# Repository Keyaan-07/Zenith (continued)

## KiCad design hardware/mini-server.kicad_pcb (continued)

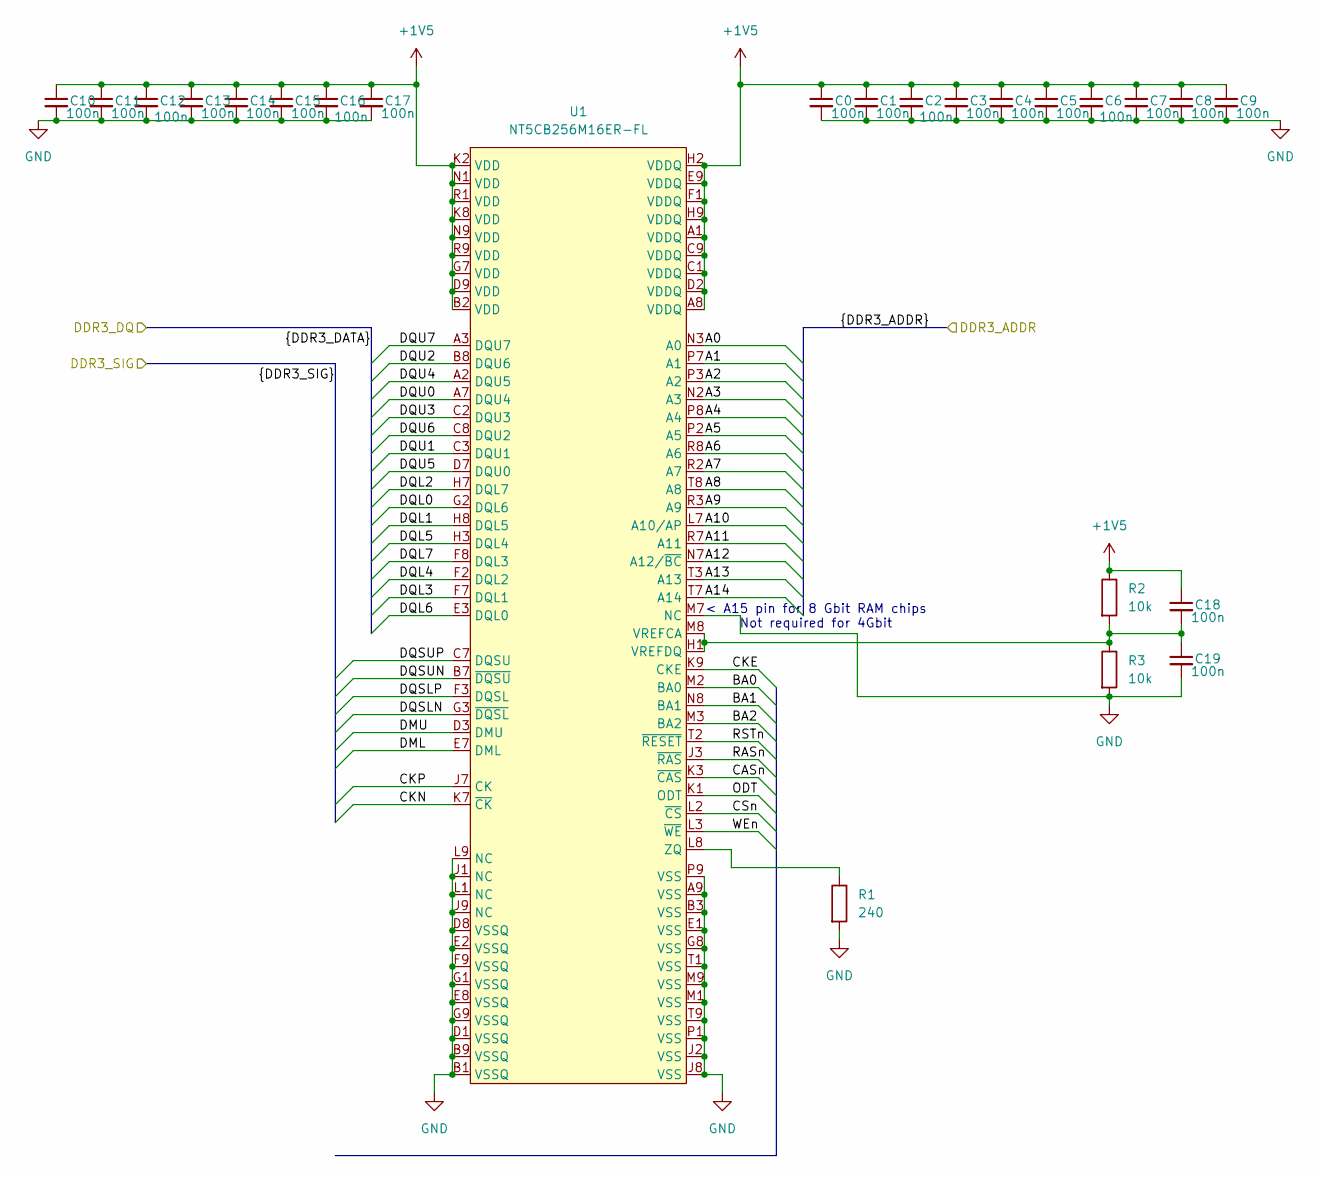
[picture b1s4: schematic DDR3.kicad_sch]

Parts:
C0, C1, C2, C3, C4, C5, C6, C7, C8, C9, C10, C11, C12, C13, C14, C15, C16, C17, C18, C19: 100n; C_0201_0603Metric
R1: 240; R_0201_0603Metric
R2, R3: 10k; R_0201_0603Metric
U1: NT5CB256M16ER-FL; TFBGA-96_L13.0-W8.0-R16-C6-P0.80-TL; MPN NT5CB256M16ER-FL; LCSC Part C2841154

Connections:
+1V5: C0.1, C1.1, C2.1, C3.1, C4.1, C5.1, C6.1, C7.1, C8.1, C9.1, C10.1, C11.1, C12.1, C13.1, C14.1, C15.1, C16.1, C17.1, C18.1, R2.1, U1.A1 (VDDQ), U1.A8 (VDDQ), U1.B2 (VDD), U1.C1 (VDDQ), U1.C9 (VDDQ), U1.D2 (VDDQ), U1.D9 (VDD), U1.E9 (VDDQ), U1.F1 (VDDQ), U1.G7 (VDD), U1.H2 (VDDQ), U1.H9 (VDDQ), U1.K2 (VDD), U1.K8 (VDD), U1.N1 (VDD), U1.N9 (VDD), U1.R1 (VDD), U1.R9 (VDD); also elsewhere on the board
/DDR3/A0: U1.N3 (A0); also elsewhere on the board
/DDR3/A1: U1.P7 (A1); also elsewhere on the board
/DDR3/A2: U1.P3 (A2); also elsewhere on the board
/DDR3/A3: U1.N2 (A3); also elsewhere on the board
/DDR3/A4: U1.P8 (A4); also elsewhere on the board
/DDR3/A5: U1.P2 (A5); also elsewhere on the board
/DDR3/A6: U1.R8 (A6); also elsewhere on the board
/DDR3/A7: U1.R2 (A7); also elsewhere on the board
/DDR3/A8: U1.T8 (A8); also elsewhere on the board
/DDR3/A9: U1.R3 (A9); also elsewhere on the board
/DDR3/A10: U1.L7 (A10/AP); also elsewhere on the board
/DDR3/A11: U1.R7 (A11); also elsewhere on the board
/DDR3/A12: U1.N7 (A12/~BC); also elsewhere on the board
/DDR3/A13: U1.T3 (A13); also elsewhere on the board
/DDR3/A14: U1.T7 (A14); also elsewhere on the board
/DDR3/BA0: U1.M2 (BA0); also elsewhere on the board
/DDR3/BA1: U1.N8 (BA1); also elsewhere on the board
/DDR3/BA2: U1.M3 (BA2); also elsewhere on the board
/DDR3/CASn: U1.K3 (~CAS); also elsewhere on the board
/DDR3/CKE: U1.K9 (CKE); also elsewhere on the board
/DDR3/CKN: U1.K7 (~CK); also elsewhere on the board
/DDR3/CKP: U1.J7 (CK); also elsewhere on the board
/DDR3/CSn: U1.L2 (~CS); also elsewhere on the board
/DDR3/DML: U1.E7 (DML); also elsewhere on the board
/DDR3/DMU: U1.D3 (DMU); also elsewhere on the board
/DDR3/DQL0: U1.G2 (DQL6); also elsewhere on the board
/DDR3/DQL1: U1.H8 (DQL5); also elsewhere on the board
/DDR3/DQL2: U1.H7 (DQL7); also elsewhere on the board
/DDR3/DQL3: U1.F7 (DQL1); also elsewhere on the board
/DDR3/DQL4: U1.F2 (DQL2); also elsewhere on the board
/DDR3/DQL5: U1.H3 (DQL4); also elsewhere on the board
/DDR3/DQL6: U1.E3 (DQL0); also elsewhere on the board
/DDR3/DQL7: U1.F8 (DQL3); also elsewhere on the board
/DDR3/DQSLN: U1.G3 (~DQSL); also elsewhere on the board
/DDR3/DQSLP: U1.F3 (DQSL); also elsewhere on the board
/DDR3/DQSUN: U1.B7 (~DQSU); also elsewhere on the board
/DDR3/DQSUP: U1.C7 (DQSU); also elsewhere on the board
/DDR3/DQU0: U1.A7 (DQU4); also elsewhere on the board
/DDR3/DQU1: U1.C3 (DQU1); also elsewhere on the board
/DDR3/DQU2: U1.B8 (DQU6); also elsewhere on the board
/DDR3/DQU3: U1.C2 (DQU3); also elsewhere on the board
/DDR3/DQU4: U1.A2 (DQU5); also elsewhere on the board
/DDR3/DQU5: U1.D7 (DQU0); also elsewhere on the board
/DDR3/DQU6: U1.C8 (DQU2); also elsewhere on the board
/DDR3/DQU7: U1.A3 (DQU7); also elsewhere on the board
/DDR3/ODT: U1.K1 (ODT); also elsewhere on the board
/DDR3/RASn: U1.J3 (~RAS); also elsewhere on the board
/DDR3/RSTn: U1.T2 (~RESET); also elsewhere on the board
/DDR3/WEn: U1.L3 (~WE); also elsewhere on the board
GND: C0.2, C1.2, C2.2, C3.2, C4.2, C5.2, C6.2, C7.2, C8.2, C9.2, C10.2, C11.2, C12.2, C13.2, C14.2, C15.2, C16.2, C17.2, C19.2, R1.2, R3.2, U1.A9 (VSS), U1.B1 (VSSQ), U1.B3 (VSS), U1.B9 (VSSQ), U1.D1 (VSSQ), U1.D8 (VSSQ), U1.E1 (VSS), U1.E2 (VSSQ), U1.E8 (VSSQ), U1.F9 (VSSQ), U1.G1 (VSSQ), U1.G8 (VSS), U1.G9 (VSSQ), U1.J1 (NC), U1.J2 (VSS), U1.J8 (VSS), U1.J9 (NC), U1.L1 (NC), U1.L9 (NC), U1.M1 (VSS), U1.M7 (NC), U1.M9 (VSS), U1.P1 (VSS), U1.P9 (VSS), U1.T1 (VSS), U1.T9 (VSS); also elsewhere on the board
unnamed: C18.2, C19.1, R2.2, R3.1, U1.H1 (VREFDQ), U1.M8 (VREFCA)
unnamed: R1.1, U1.L8 (ZQ)

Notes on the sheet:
< A15 pin for 8 Gbit RAM chips Not required for 4Gbit

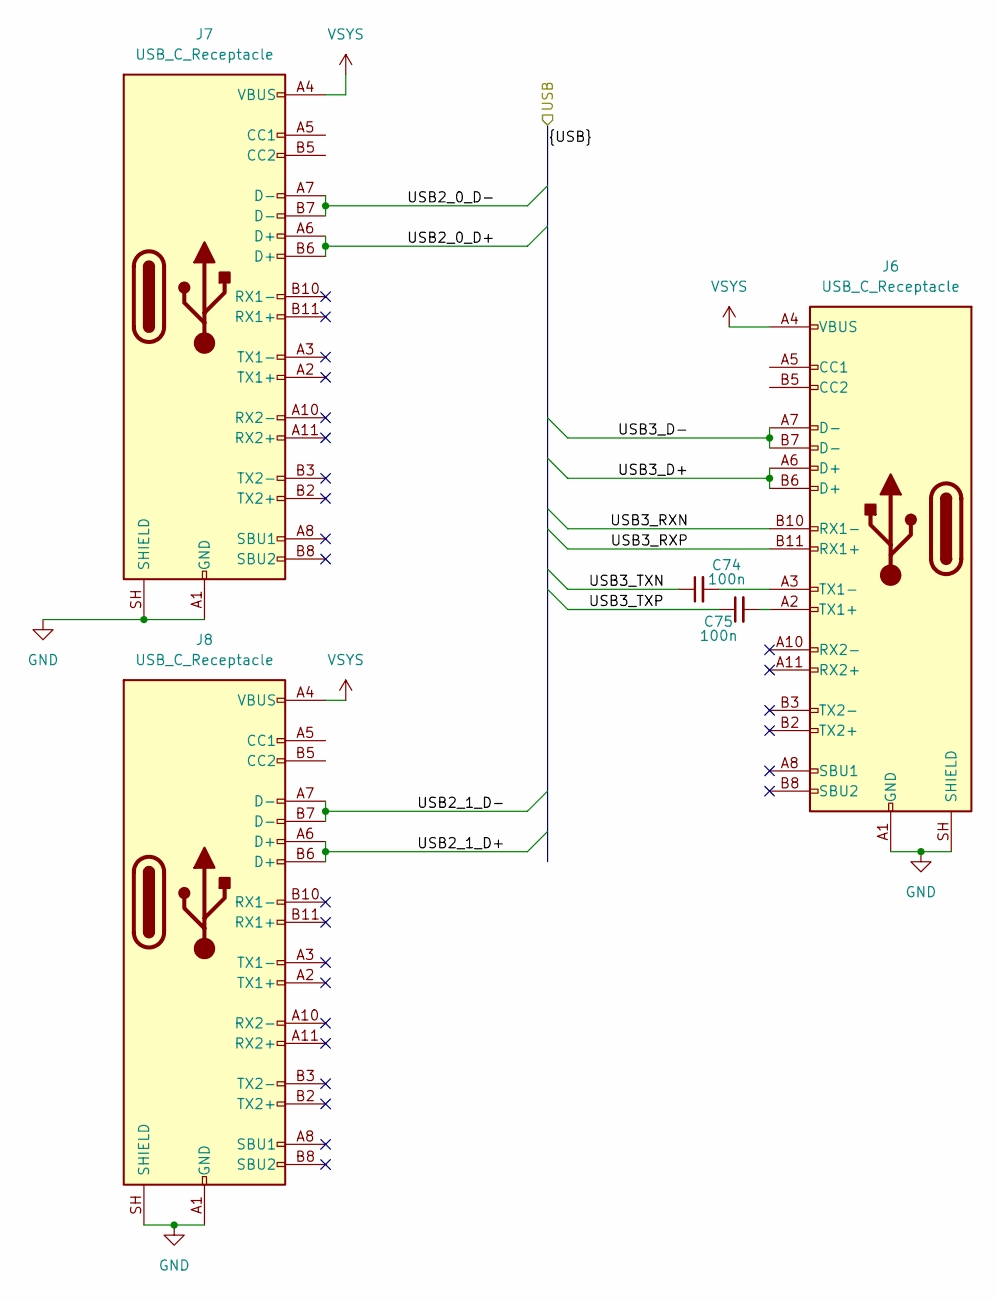
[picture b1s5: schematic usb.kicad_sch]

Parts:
C74, C75: 100n; C_0201_0603Metric
J6, J7, J8: USB_C_Receptacle; USB_C_Receptacle_Molex_105450-0101

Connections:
/USB/USB2_0_D+: J7.A6 (D+), J7.B6 (D+); also elsewhere on the board
/USB/USB2_0_D-: J7.A7 (D-), J7.B7 (D-); also elsewhere on the board
/USB/USB2_1_D+: J8.A6 (D+), J8.B6 (D+); also elsewhere on the board
/USB/USB2_1_D-: J8.A7 (D-), J8.B7 (D-); also elsewhere on the board
/USB/USB3_D+: J6.A6 (D+), J6.B6 (D+); also elsewhere on the board
/USB/USB3_D-: J6.A7 (D-), J6.B7 (D-); also elsewhere on the board
/USB/USB3_RXN: J6.B10 (RX1-); also elsewhere on the board
/USB/USB3_RXP: J6.B11 (RX1+); also elsewhere on the board
/USB/USB3_TXN: C74.1; also elsewhere on the board
/USB/USB3_TXP: C75.1; also elsewhere on the board
GND: J6.A1 (GND), J6.A12 (GND), J6.B1 (GND), J6.B12 (GND), J6.SH (SHIELD), J7.A1 (GND), J7.A12 (GND), J7.B1 (GND), J7.B12 (GND), J7.SH (SHIELD), J8.A1 (GND), J8.A12 (GND), J8.B1 (GND), J8.B12 (GND), J8.SH (SHIELD); also elsewhere on the board
unnamed: C75.2, J6.A2 (TX1+)
unnamed: C74.2, J6.A3 (TX1-)
VSYS: J6.A4 (VBUS), J6.A9 (VBUS), J6.B4 (VBUS), J6.B9 (VBUS), J7.A4 (VBUS), J7.A9 (VBUS), J7.B4 (VBUS), J7.B9 (VBUS), J8.A4 (VBUS), J8.A9 (VBUS), J8.B4 (VBUS), J8.B9 (VBUS); also elsewhere on the board

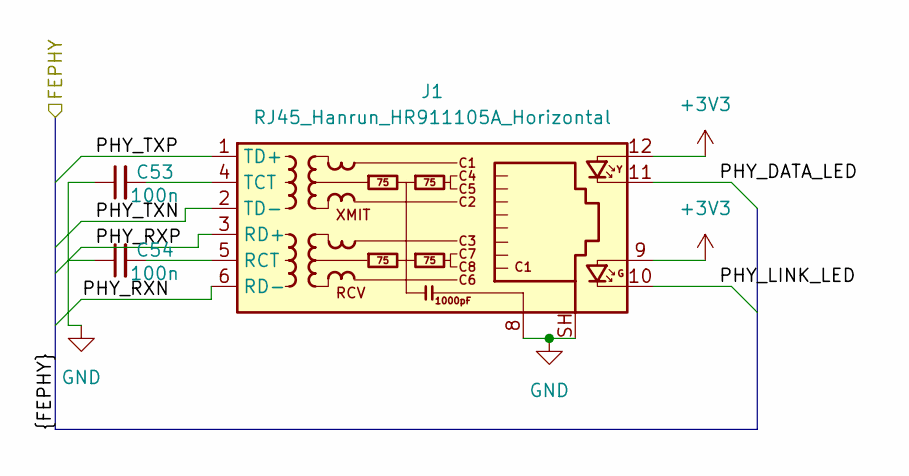
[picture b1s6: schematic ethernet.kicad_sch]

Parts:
C53, C54: 100n; C_0201_0603Metric
J1: RJ45_Hanrun_HR911105A_Horizontal

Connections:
+3V3: J1.9, J1.12; also elsewhere on the board
/Ethernet/PHY_DATA_LED: J1.11; also elsewhere on the board
/Ethernet/PHY_LINK_LED: J1.10; also elsewhere on the board
/Ethernet/PHY_RXN: J1.6 (RD-); also elsewhere on the board
/Ethernet/PHY_RXP: J1.3 (RD+); also elsewhere on the board
/Ethernet/PHY_TXN: J1.2 (TD-); also elsewhere on the board
/Ethernet/PHY_TXP: J1.1 (TD+); also elsewhere on the board
GND: C53.1, C54.1, J1.8, J1.SH; also elsewhere on the board
unnamed: C54.2, J1.5 (RCT)
unnamed: C53.2, J1.4 (TCT)

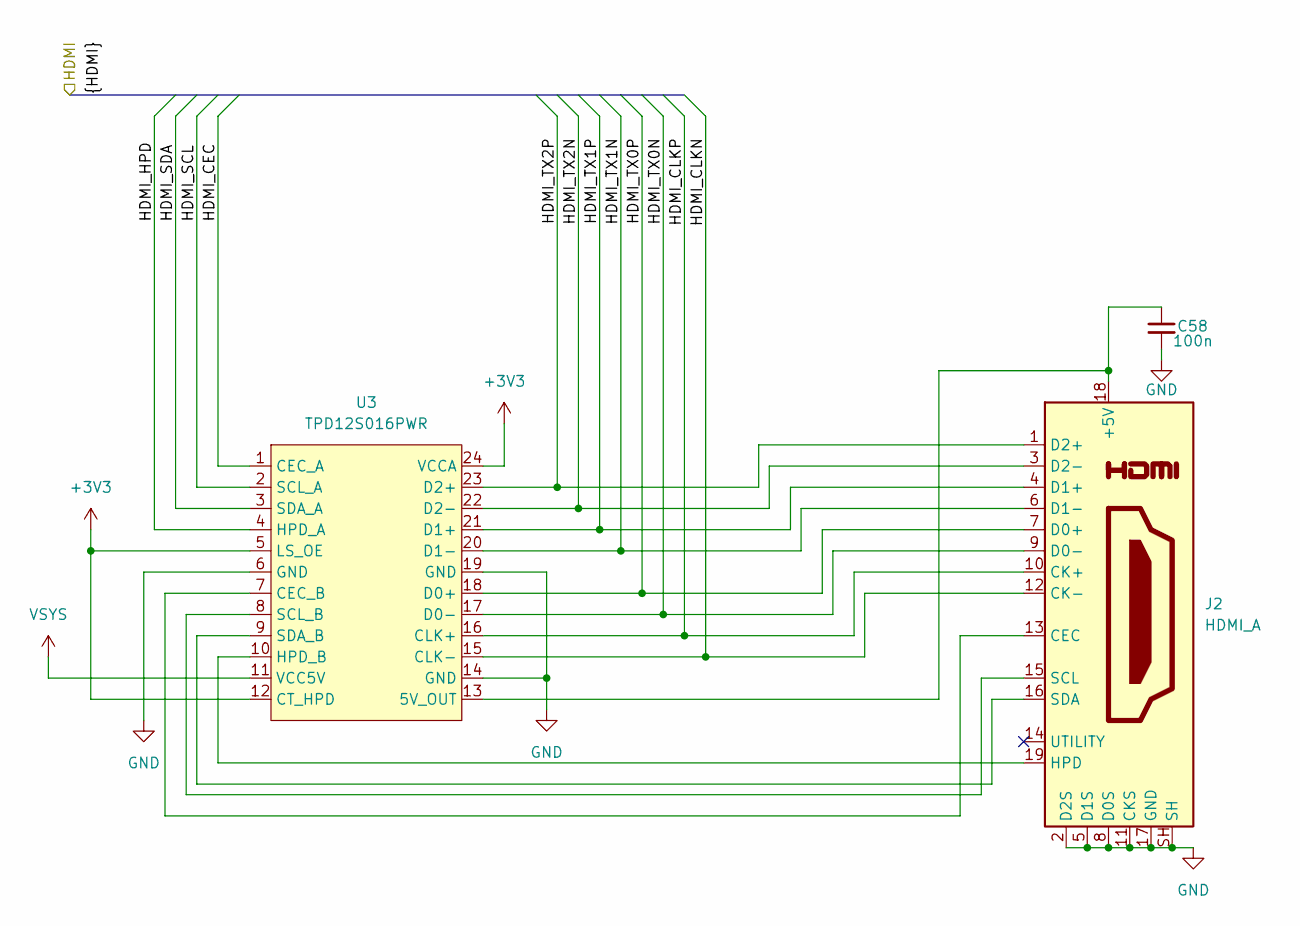
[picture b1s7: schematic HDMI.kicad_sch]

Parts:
C58: 100n; C_0201_0603Metric
J2: HDMI_A; HDMI_A_Molex_208658-1001_Horizontal
U3: TPD12S016PWR; TSSOP-24_L7.8-W4.4-P0.65-LS6.4-BL; MPN TPD12S016PWR; LCSC Part C201665

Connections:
+3V3: U3.5 (LS_OE), U3.12 (CT_HPD), U3.24 (VCCA); also elsewhere on the board
/HDMI/HDMI_CEC: U3.1 (CEC_A); also elsewhere on the board
/HDMI/HDMI_CLKN: J2.12 (CK-), U3.15 (CLK-); also elsewhere on the board
/HDMI/HDMI_CLKP: J2.10 (CK+), U3.16 (CLK+); also elsewhere on the board
/HDMI/HDMI_HPD: U3.4 (HPD_A); also elsewhere on the board
/HDMI/HDMI_SCL: U3.2 (SCL_A); also elsewhere on the board
/HDMI/HDMI_SDA: U3.3 (SDA_A); also elsewhere on the board
/HDMI/HDMI_TX0N: J2.9 (D0-), U3.17 (D0-); also elsewhere on the board
/HDMI/HDMI_TX0P: J2.7 (D0+), U3.18 (D0+); also elsewhere on the board
/HDMI/HDMI_TX1N: J2.6 (D1-), U3.20 (D1-); also elsewhere on the board
/HDMI/HDMI_TX1P: J2.4 (D1+), U3.21 (D1+); also elsewhere on the board
/HDMI/HDMI_TX2N: J2.3 (D2-), U3.22 (D2-); also elsewhere on the board
/HDMI/HDMI_TX2P: J2.1 (D2+), U3.23 (D2+); also elsewhere on the board
GND: C58.2, J2.2 (D2S), J2.5 (D1S), J2.8 (D0S), J2.11 (CKS), J2.17 (GND), J2.SH, U3.6 (GND), U3.14 (GND), U3.19 (GND); also elsewhere on the board
unnamed: C58.1, J2.18 (+5V), U3.13 (5V_OUT)
unnamed: J2.13 (CEC), U3.7 (CEC_B)
unnamed: J2.19 (HPD), U3.10 (HPD_B)
unnamed: J2.15 (SCL), U3.8 (SCL_B)
unnamed: J2.16 (SDA), U3.9 (SDA_B)
VSYS: U3.11 (VCC5V); also elsewhere on the board

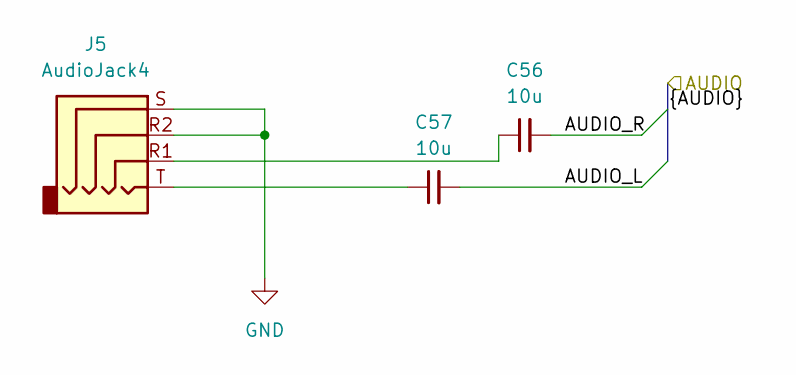
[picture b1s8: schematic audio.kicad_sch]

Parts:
C56, C57: 10u; C_0603_1608Metric
J5: AudioJack4; Jack_3.5mm_KoreanHropartsElec_PJ-320D-4A_Horizontal

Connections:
/Audio/AUDIO_L: C57.2; also elsewhere on the board
/Audio/AUDIO_R: C56.2; also elsewhere on the board
GND: J5.R2, J5.S; also elsewhere on the board
unnamed: C56.1, J5.R1
unnamed: C57.1, J5.T

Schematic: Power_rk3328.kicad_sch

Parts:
C21, C22, C23, C24, C25, C26, C27, C28, C29, C30, C31, C32, C33: 100n; C_0201_0603Metric
U2: RK3328; TFBGA395_L14.0-W14.0_RK3328; MPN RK3328; LCSC Part C2932939

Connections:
+1V0: C21.1, C22.1, C23.1, C24.1, C25.1, C26.1, C27.1, C28.1, C29.1, C30.1, C31.1, C32.1, C33.1, U2.H7 (PLL_DVDD_1V0), U2.J7 (USB30_DVDD_1V0), U2.M6 (HDMI_AVDD_1V0), U2.N9 (VDD_LOGIC_1), U2.N10 (VDD_LOGIC_2), U2.N11 (VDD_LOGIC_3), U2.P9 (VDD_LOGIC_4), U2.P10 (VDD_LOGIC_5), U2.P11 (VDD_LOGIC_6), U2.P13 (VDD_CORE_1), U2.P14 (VDD_CORE_2), U2.R9 (VDD_LOGIC_7), U2.R10 (VDD_LOGIC_8), U2.R11 (VDD_LOGIC_9), U2.R13 (VDD_CORE_3), U2.R14 (VDD_CORE_4), U2.T13 (VDD_CORE_5), U2.T14 (VDD_CORE_6), U2.T15 (VDD_CORE_7), U2.V5 (USB20_DVDD_1V0), U2.V6 (FEPHY_AVDD_1V0); also elsewhere on the board
+1V5: U2.F10 (VDD_DDRIO_1), U2.F11 (VDD_DDRIO_2), U2.F12 (VDD_DDRIO_3), U2.F13 (VDD_DDRIO_4), U2.G10 (VDD_DDRIO_5), U2.G11 (VDD_DDRIO_6), U2.G12 (VDD_DDRIO_7), U2.G13 (VDD_DDRIO_8), U2.H16 (VDD_DDRIO_9), U2.J15 (VDD_DDRIO_10), U2.J16 (VDD_DDRIO_11), U2.K15 (VDD_DDRIO_12), U2.K16 (VDD_DDRIO_13); also elsewhere on the board
+1V8: U2.H5 (PLL_AVDD_1V8), U2.J5 (USB30_AVDD_1V8), U2.M16 (SARADC_AVDD_1V8), U2.N5 (CODEC_AVDD_1V8), U2.N6 (VDAC_AVDD_1V8), U2.P6 (HDMI_AVDD_1V8), U2.U5 (USB20_AVDD_1V8), U2.U6 (FEPHY_AVDD_1V8); also elsewhere on the board
+3V3: U2.H6 (VCCIO6), U2.J6 (USB30_AVDD_3V3), U2.K6 (VCCIO_PMU), U2.R16 (VCCIO5), U2.T5 (USB20_AVDD_3V3), U2.T7 (VCCIO1), U2.T17 (VCCIO2), U2.U7 (VCCIO3), U2.U12 (VCCIO4); also elsewhere on the board
GND: C21.2, C22.2, C23.2, C24.2, C25.2, C26.2, C27.2, C28.2, C29.2, C30.2, C31.2, C32.2, C33.2, U2.A1 (VSS1), U2.A21 (VSS2), U2.AA1 (VSS151), U2.AA5 (VSS152), U2.AA21 (VSS153), U2.B4 (VSS3), U2.B14 (VSS4), U2.B16 (VSS5), U2.C1 (VSS6), U2.C3 (VSS7), U2.C6 (VSS8), U2.C9 (VSS9), U2.C11 (VSS10), U2.C14 (VSS11), U2.C17 (VSS12), U2.C18 (VSS13), U2.C19 (VSS14), U2.D3 (VSS15), U2.D6 (VSS16), U2.D8 (VSS17), U2.D11 (VSS18), U2.D14 (VSS19), U2.D17 (VSS20), U2.D18 (VSS21), U2.E4 (VSS22), U2.E5 (VSS23), U2.E6 (VSS24), U2.E7 (VSS25), U2.E8 (VSS26), U2.E9 (VSS27), U2.E10 (VSS28), U2.E11 (VSS29), U2.E12 (VSS30), U2.E13 (VSS31), U2.E14 (VSS32), U2.E15 (VSS33), U2.E16 (VSS34), U2.E17 (VSS35), U2.E19 (VSS36), U2.F4 (VSS37), U2.F5 (VSS38), U2.F6 (VSS39), U2.F7 (VSS40), U2.F8 (VSS41), U2.F9 (VSS42), U2.F17 (VSS43), U2.F20 (VSS44), U2.G2 (VSS45), U2.G3 (VSS46), U2.G4 (VSS47), U2.G6 (VSS48), U2.G7 (VSS49), U2.G8 (VSS50), U2.G9 (VSS51), U2.G14 (VSS52), U2.G15 (VSS53), U2.G17 (VSS54), U2.G18 (VSS55), U2.H4 (VSS56), U2.H8 (VSS57), U2.H9 (VSS58), U2.H10 (VSS59), U2.H11 (VSS60), U2.H12 (VSS61), U2.H13 (VSS62), U2.H14 (VSS63), U2.H15 (VSS64), U2.H17 (VSS65), U2.J4 (VSS66), U2.J8 (VSS67), U2.J9 (VSS68), U2.J10 (VSS69), U2.J11 (VSS70), U2.J12 (VSS71), U2.J13 (VSS72), U2.J14 (VSS73), U2.J17 (VSS74), U2.J20 (VSS75), U2.K3 (VSS76), U2.K5 (VSS77), U2.K8 (VSS78), U2.K9 (VSS79), U2.K10 (VSS80), U2.K11 (VSS81), U2.K12 (VSS82), U2.K13 (VSS83), U2.K14 (VSS84), U2.K17 (VSS85), U2.L4 (VSS86), U2.L5 (VSS87), U2.L6 (VSS88), U2.L7 (VSS89), U2.L8 (VSS90), U2.L9 (VSS91), U2.L10 (VSS92), U2.L11 (VSS93), U2.L12 (VSS94), U2.L13 (VSS95), U2.L14 (VSS96), U2.L15 (VSS97), U2.L16 (VSS98), U2.L17 (VSS99), U2.L21 (VSS100), U2.M7 (VSS101), U2.M8 (VSS102), U2.M9 (VSS103), U2.M10 (VSS104), U2.M11 (VSS105), U2.M12 (VSS106), U2.M13 (VSS107), U2.M14 (VSS108), U2.N3 (VSS109), U2.N7 (VSS110), U2.N8 (VSS111), U2.N12 (VSS112), U2.N13 (VSS113), U2.N14 (VSS114), U2.N15 (VSS115), U2.P3 (VSS116), U2.P7 (VSS117), U2.P8 (VSS118), U2.P12 (VSS119), U2.P15 (VSS120), U2.R2 (VSS121), U2.R4 (CODEC_AVSS), U2.R5 (VSS122), U2.R7 (VSS123), U2.R8 (VSS124), U2.R12 (VSS125), U2.R15 (VSS126), U2.T2 (VSS127), U2.T3 (VSS128), U2.T8 (VSS129), U2.T9 (VSS130), U2.T10 (VSS131), U2.T11 (VSS132), U2.T12 (VSS133), U2.U4 (VSS134), U2.U8 (VSS135), U2.U9 (VSS136), U2.U11 (VSS137), U2.U13 (VSS138), U2.U14 (VSS139), U2.U15 (VSS140), U2.V4 (VSS141), U2.V8 (VSS142), U2.V11 (VSS143), U2.W1 (VSS144), U2.W3 (VSS145), U2.W4 (VSS146), U2.W5 (VSS147), U2.W7 (VSS148), U2.W8 (VSS149), U2.W9 (VSS150); also elsewhere on the board

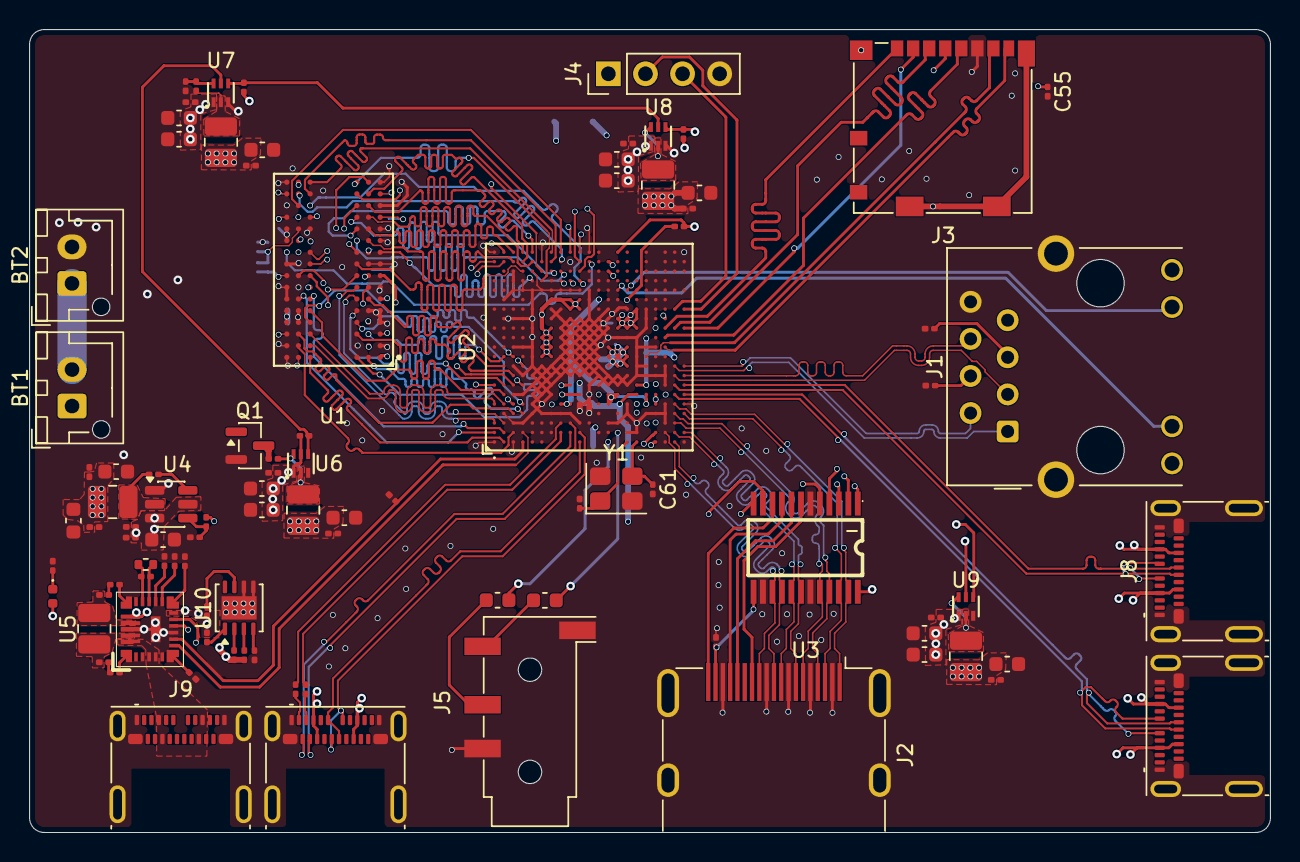
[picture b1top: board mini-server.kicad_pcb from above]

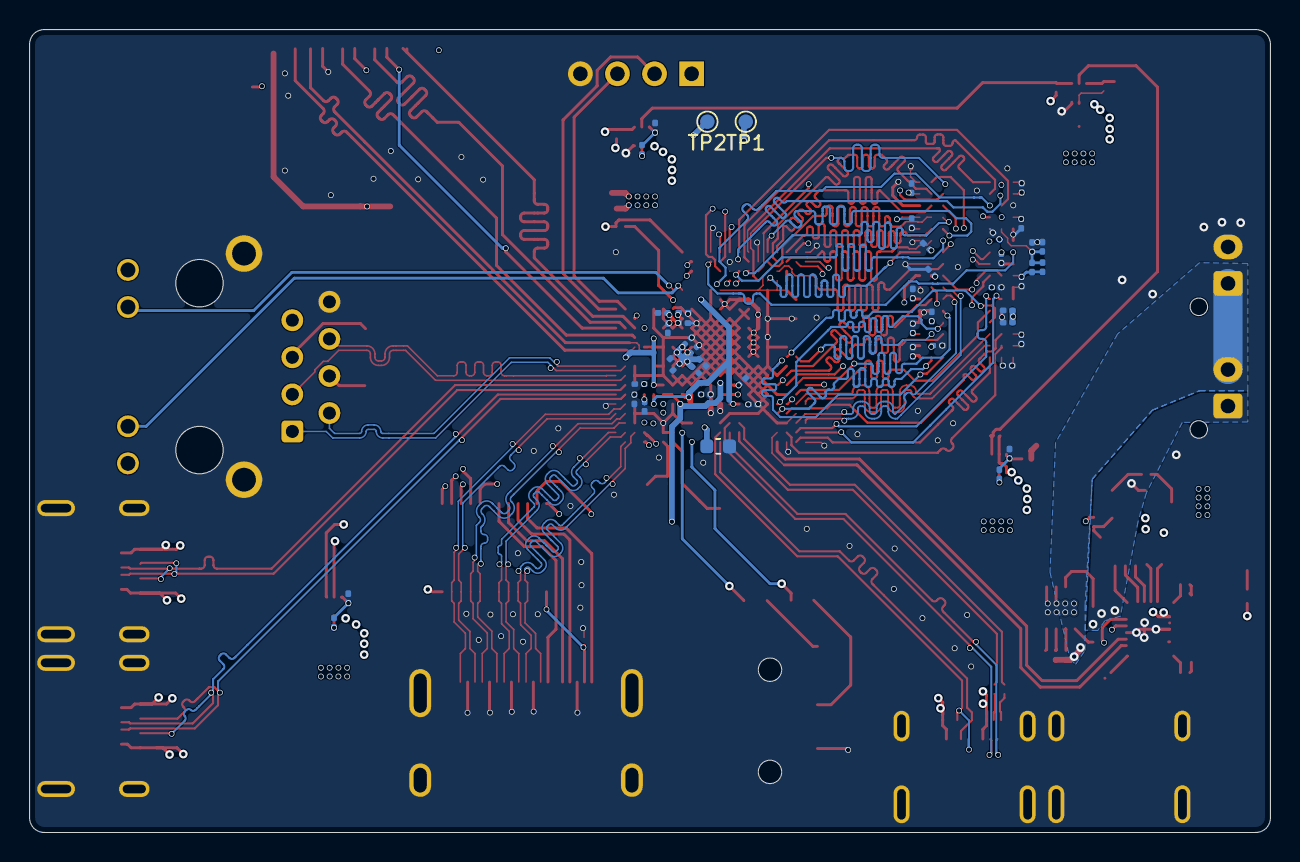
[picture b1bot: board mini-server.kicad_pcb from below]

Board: 6 copper layers, 85.0 x 55.0 mm, 142 parts (48 on the bottom side), 156 nets.

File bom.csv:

Designator,Function,Value,Quantity,Price,Amount,Link
PCB,PCB,85x55mm,5,9.6,48,https://jlcpcb.com/
PCBA,Standard,PCBA,2,42.75,85.5,https://jlcpcb.com/
"BT1, BT2",Battery Connectors,Battery_Cell,4,,0,
"C0, C1, C10, C11, C12, C13, C14, C15, C16, C17, C18, C19, C2, C21, C22, C23, C24, C25, C26, C27, C28, C29, C3, C30, C31, C32, C33, C35, C37, C4, C40, C42, C47, C48, C5, C51, C52, C53, C54, C55, C58, C6, C62, C64, C67, C7, C70, C71, C74, C75, C8, C9",Capacitor,100n,104,0.001,0.104,https://www.lcsc.com/product-detail/C49062.html
"C20, C34, C36, C38, C39, C41, C43, C44, C45, C46, C49, C50, C56, C57, C59, C63, C66",Capacitor,10u,34,0.03,1.02,https://www.lcsc.com/product-detail/C96446.html
"C60, C61",Capacitor,15p,4,0.0013,0.0052,https://www.lcsc.com/product-detail/C277480.html
"C65, C68",Capacitor,1u,4,0.009,0.036,https://www.lcsc.com/product-detail/C307385.html
"C72, C73",Capacitor,47n,4,0.0044,0.0176,https://www.lcsc.com/product-detail/C2930549.html
D1,LED,LED,2,0.009,0.018,https://www.lcsc.com/product-detail/C7496805.html
J1,Ethernet magjack,-,2,1.5,3,https://www.lcsc.com/product-detail/C12074.html
J2,HDMI,-,2,1.5,3,https://www.lcsc.com/product-detail/C916313.html
J3,Micro SD Connector,-,2,0.68,1.36,https://www.lcsc.com/product-detail/C585350.html
J4,UART header,-,2,DNP,DNP,DNP
J5,Audiojack,-,2,0.05,0.1,https://www.lcsc.com/product-detail/C431535.html
"J6, J7, J8, J9",USB-C,-,8,0.5,4,https://www.lcsc.com/product-detail/C5156605.html
"L1, L2, L3, L4, L5, L6",Inductors,2.2u,12,0.03,0.36,https://www.lcsc.com/product-detail/C45385204.html
Q1,MOSFET,2N7002,2,0.05,0.1,https://www.lcsc.com/product-detail/C81445.html
Q2,MOSFET,AON7262e,2,0.58,1.16,https://www.lcsc.com/product-detail/C176755.html
R1,Resistor,240,2,0.0009,0.0018,https://www.lcsc.com/product-detail/C270354.html
"R11, R17, R2, R26, R27, R3, R30, R31, R32, R33, R35, R38, R40, R5, R6, R8, R9",Resistor,10k,34,0.0007,0.0238,https://www.lcsc.com/product-detail/C7467266.html
"R12, R41",Resistor,35k,4,0.0015,0.006,https://www.lcsc.com/product-detail/C180320.html
"R13, R14, R15, R18, R19, R20",Resistor,R,12,-,0,-
R16,Resistor,56k,2,0.0008,0.0016,https://www.lcsc.com/product-detail/C18164325.html
R21,Resistor,10m,2,0.14,0.28,https://www.lcsc.com/product-detail/C6250315.html
"R22, R23, R24, R25, R34",Resistor,100,10,0.0009,0.009,https://www.lcsc.com/product-detail/C270366.html
"R28, R29",Resistor,0R,4,0.0009,0.0036,https://www.lcsc.com/product-detail/C106228.html
"R36, R37, R39",Resistor,5.1k,6,0.0007,0.0042,https://www.lcsc.com/product-detail/C7467269.html
R4,Resistor,6.6k,2,0.0008,0.0016,https://www.lcsc.com/product-detail/C423452.html
U1,RAM,NT5CB256M16ER-FL,2,13.15,26.3,https://www.lcsc.com/product-detail/C2841154.html
U10,SoC,BQ29209DRBR,2,0.76,1.52,https://www.lcsc.com/product-detail/C139352.html
U2,main IC,RK3328,2,8.65,17.3,https://www.lcsc.com/product-detail/C2932939.html
U3,ESD IC for HDMI,TPD12S016PWR,2,0.8382,1.6764,https://www.lcsc.com/product-detail/C201665.html
U4,Buck,TPS565201,2,0.64,1.28,https://www.lcsc.com/product-detail/C327676.html
U5,Battery charger,BQ25690RBAR,2,6.3,12.6,https://www.lcsc.com/product-detail/C53283868.html
"U6, U7, U8, U9",Buck,TPS563252DRLR,8,1.05,8.4,https://www.lcsc.com/product-detail/C19188399.html
Y1,Crystal,24MHz,2,0.58,1.16,https://www.lcsc.com/product-detail/C41383245.html
,,,,,,
,,,,,,
,,,,,,
,,,,,134.8488,

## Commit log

2026-04-19 hello world
2026-04-21 Made a new power schematic and a new DDR4 ram schematic
2026-04-22 DDR4 schematic almost completed
2026-05-08 New SoC
2026-05-09 Address and Control signals of DDR3 ram routed
2026-05-11 DQ lines routed from the RK3328 to DDR3 RAM
2026-05-11 Images
2026-05-13 stuff
2026-05-16 Routing and PCB
2026-05-16 component Placement
2026-05-21 routing
2026-05-25 New battery charger IC
2026-05-29 routing and power pours
2026-06-01 touch up on lots of small things
2026-06-03 final touches
2026-06-03 pcb step file
2026-06-03 added gitignore
2026-06-03 Create LICENSE
2026-06-03 PCB step files
2026-06-03 prod files
2026-06-03 Upload images
2026-06-03 new prod files
2026-06-03 README
2026-06-03 change images
2026-06-03 resistor values fixed
2026-06-03 update readme with BOM data
2026-06-03 fixed error
2026-06-03 add onshape link
2026-06-03 added zine page
